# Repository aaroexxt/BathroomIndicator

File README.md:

# BathroomIndicator
 BLISS - Bathroom Location and Indication Security System aka an overcomplicated way to prevent accidental walk-ins, and a great PCB learning project!

## Design Intent
I built this mostly to practice my PCB design and layout skills, but it's actually quite cool in person. Basically, it's designed to be a comprehensive system for people who have to share space to have a way to tell others that they're busy. I've installed a set of these on a bathroom I share with my sister (who thought that was a good idea?) so that we can both know when somebody else is using the bathroom.

## Pictures

Version 1

Version 2

## Renderings

Top - Version 2

Bottom - Version 2

### Design Notes

The major difference between versions 1 and 2 is that Version 1 had a custom radio based on the NRF24L01+ radio by Nordic Semiconductor, while this was replaced with a premade module in Version 2 because of my lack of experience with antenna design (1 foot range on my custom one vs _30_ feet on the premade module). Other than that, it worked well. I also had some issues with the 3.3v regulator schematic in V1 (incorrect schematic for EN pin) but this was solved in version 2.

### By Aaron Becker

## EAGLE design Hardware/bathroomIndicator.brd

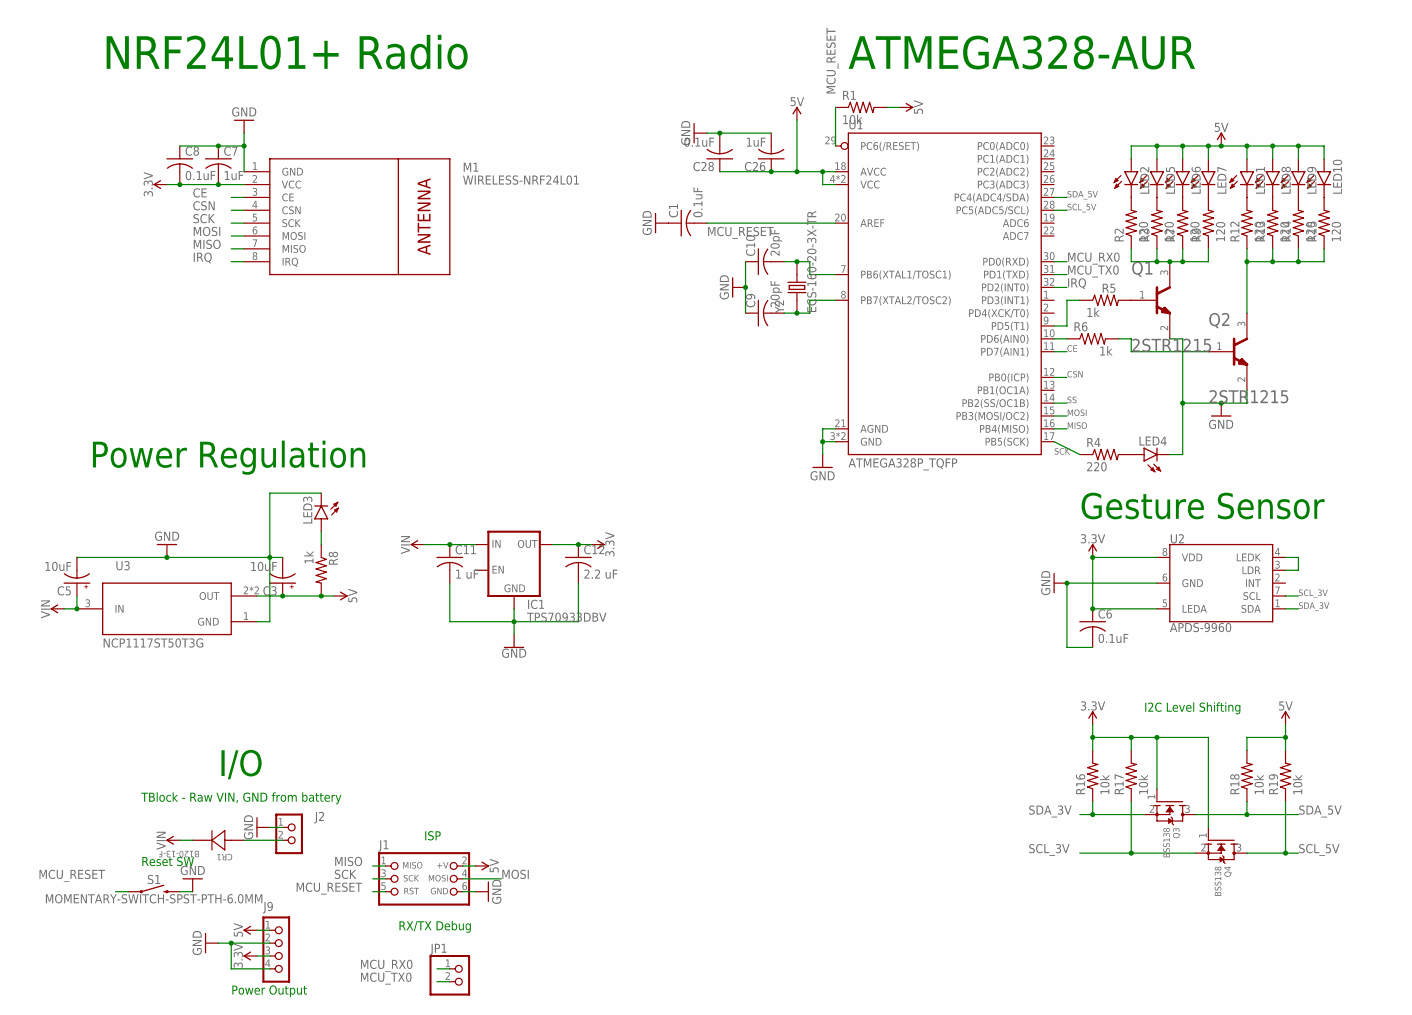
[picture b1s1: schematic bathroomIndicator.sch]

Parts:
C1, C6, C8, C28: 0.1uF; C0805
C3, C5: 10uF; B/3528-21W
C7, C26: 1uF; C0805
C9, C10: 20pF; C0805
C11: 1 uF; C0805
C12: 2.2 uF; C0805
CR1: B120-13-F; SMA_DIO
IC1: TPS70933DBV; SOT23-5
J1: CON_HEADER_PRG_AVR_ICSP-PTH; HEADER_PRG_2X03
J2: CON_TERMINAL_BLOCK_02-5MM; TERMINAL_BLOCK_2P_5
J9: CON_HEADER_1X04; M1X4
JP1: HEADER-1X2ROUND; 1X02_ROUND
LED1, LED2, LED5, LED6, LED7, LED8, LED9, LED10: LED5MM
LED3, LED4: LEDSML0805; SML0805
M1: WIRELESS-NRF24L01
Q1, Q2: STMICROELECTRONICS_2STR1215STMICROELECTRONICS_2ST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; STMICROELECTRONICS_2STR1215_0
Q3, Q4: BSS138; SOT23-WIDE
R1, R16, R17, R18, R19: 10k; R0805
R2, R3, R7, R9, R12, R13, R14, R15: 120; R0805
R4: 220; R0805
R5, R6, R8: 1k; R0805
S1: MOMENTARY-SWITCH-SPST-PTH-6.0MM; TACTILE_SWITCH_PTH_6.0MM
U1: ATMEGA328P_TQFP; TQFP32-08
U2: APDS-9960
U3: NCP1117ST50T3G; SOT230P700X180-4N
Y2: ECS-160-20-3X-TR; XTAL_ECS-160-20-3X-TR

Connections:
3.3V: C6.1, C7.2, C8.2, C12.1, IC1.5 (OUT), J9.3, M1.2 (VCC), Q3.1 (G), Q4.1 (G), R16.2, R17.2, U2.5 (LEDA), U2.8 (VDD)
5V: C3.+, C26.1, C28.1, J1.2 (+V), J9.1, LED1.A, LED2.A, LED5.A, LED6.A, LED7.A, LED8.A, LED9.A, LED10.A, R1.2, R8.2, R18.2, R19.2, U1.4 (VCC), U1.6 (VCC), U1.18 (AVCC), U3.2 (OUT), U3.4 (OUT)
CE: M1.3 (CE), U1.11 (PD7(AIN1))
CSN: M1.4 (CSN), U1.12 (PB0(ICP))
GND: C1.1, C3.-, C5.-, C6.2, C7.1, C8.1, C9.1, C10.1, C11.2, C12.2, C26.2, C28.2, IC1.2 (GND), J1.6 (GND), J2.1, J9.2, J9.4, LED3.C, LED4.C, M1.1 (GND), Q1.2 (E), Q2.2 (E), S1.3 (2), U1.3 (GND), U1.5 (GND), U1.21 (AGND), U2.6 (GND), U3.1 (GND)
IRQ: M1.8 (IRQ), U1.32 (PD2(INT0))
MCU_RESET: J1.5 (RST), R1.1, S1.1, U1.29 (PC6(/RESET))
MCU_RX0: JP1.1, U1.30 (PD0(RXD))
MCU_TX0: JP1.2, U1.31 (PD1(TXD))
MISO: J1.1 (MISO), M1.7 (MISO), U1.16 (PB4(MISO))
MOSI: J1.4 (MOSI), M1.6 (MOSI), U1.15 (PB3(MOSI/OC2))
unnamed: LED2.K (C), R2.2
unnamed: LED5.K (C), R3.2
unnamed: C1.2, U1.20 (AREF)
unnamed: LED6.K (C), R7.2
unnamed: R5.1, U1.9 (PD5(T1))
unnamed: LED7.K (C), R9.2
unnamed: LED4.A, R4.2
unnamed: Q2.1 (B), R6.2
unnamed: R6.1, U1.10 (PD6(AIN0))
unnamed: LED3.A, R8.1
unnamed: Q1.1 (B), R5.2
unnamed: C9.2, U1.8 (PB7(XTAL2/TOSC2)), Y2.1
unnamed: C10.2, U1.7 (PB6(XTAL1/TOSC1)), Y2.2
unnamed: U2.3 (LDR), U2.4 (LEDK)
unnamed: LED1.K (C), R12.2
unnamed: LED8.K (C), R13.2
unnamed: LED9.K (C), R14.2
unnamed: LED10.K (C), R15.2
unnamed: Q1.3 (C), R2.1, R3.1, R7.1, R9.1
unnamed: Q2.3 (C), R12.1, R13.1, R14.1, R15.1
unnamed: CR1.2, J2.2
SCK: J1.3 (SCK), M1.5 (SCK), R4.1, U1.17 (PB5(SCK))
SCL_3V: Q4.2 (S), R17.1, U2.7 (SCL)
SCL_5V: Q4.3 (D), R19.1, U1.28 (PC5(ADC5/SCL))
SDA_3V: Q3.2 (S), R16.1, U2.1 (SDA)
SDA_5V: Q3.3 (D), R18.1, U1.27 (PC4(ADC4/SDA))
SS: U1.14 (PB2(SS/OC1B))
VIN: C5.+, C11.1, CR1.1, IC1.1 (IN), U3.3 (IN)

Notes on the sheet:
TBlock - Raw VIN, GND from battery
NRF24L01+ Radio
ATMEGA328-AUR
Power Regulation
I/O
Gesture Sensor
I2C Level Shifting
RX/TX Debug
ISP
Reset SW
Power Output

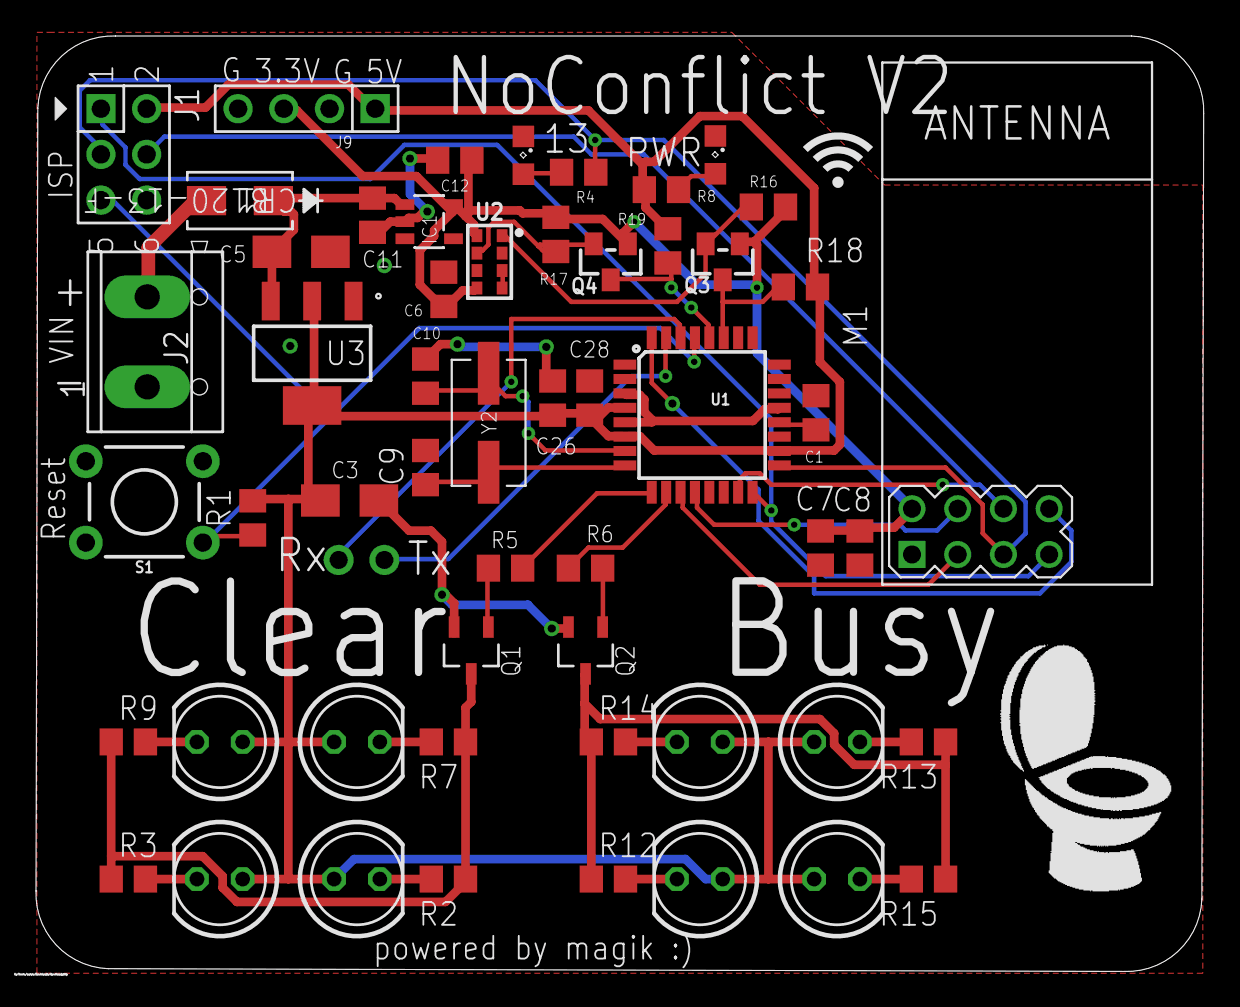
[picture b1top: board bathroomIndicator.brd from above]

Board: 2 copper layers, 64.9 x 52.0 mm, 55 parts (0 on the bottom side), 38 nets.

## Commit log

2020-09-05 upload all info
2020-09-09 added reset to clear after 20min feature
2020-09-10 final fixes

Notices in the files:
parts and their libraries:
microbuilder: This work is placed in the public domain, and may be freely used for commercial and non-commercial work with the following conditions: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
SparkFun-Switches: Licensing: Creative Commons ShareAlike 4.0 International - https://creativecommons.org/licenses/by-sa/4.0
